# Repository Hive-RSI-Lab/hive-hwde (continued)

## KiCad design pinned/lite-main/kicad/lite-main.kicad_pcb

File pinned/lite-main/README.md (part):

# lite-main: the Lite tier of hifi-receiver-2

The Lite tier's one board, as `docs/product.md` defines it. You plug a USB-C PD
laptop charger of 65 W or more and a pair of speakers into it (Lite asks for
20 V and uses at most what that contract allows, 60–65 W with an ordinary
cable: a bigger charger adds nothing; see issue #136). It streams over Wi-Fi
(Spotify Connect, AirPlay, Lyrion) and Bluetooth, takes a DJ deck on RCA, and
drives two subwoofers from RCA sub outs. A web app on your phone, three buttons
or any IR remote control it.

It was designed with the hive-hwde module (KiCad 10), from schematic to JLC fab
package, on 2026-10-28. **Nothing has been ordered.** Ordering and paying are
the person's. The workspace is named after the board, `boards/lite-main/` (the
brief said `boards/lite/`): that is the path `tools/hwcheck.py` scores, from
product.md's Boards row.

## What it is

- **Board:** 2 layers, 1.6 mm FR-4, 1 oz, OSP, 118 x 90 mm, four M3 holes
  (H1-H3 plated, H4 bare), 2 mm corners. 154 parts, all on the top side. 147 are SMT; 7 are
  through-hole (J2, J3, J4-J7 and U9). The 4 mounting holes are not BOM parts.
  JLC assembly with LCSC part numbers.
- **Rear edge, left to right:**
  - **J2:** RCA line in (FLX4). Top jack white = L, bottom red = R. ESD: D3/D4.
  - **J3:** RCA sub out L/R. ESD: D5/D6.
  - **J1:** USB-C.
  - **J4-J7:** the speaker outputs, four 4 mm banana sockets (Amass 24.243,
    right-angle PCB mount, 24 A, red C7437321 / black C7437322; JLC fits
    them): J4 L+, J5 L-, J6 R+, J7 R-, at 11 mm pitch. Their round collars
    (9.40 mm across, 2.60 mm long, bottom 3.20 mm over the board) reach 2.65 mm
    past the rear edge into the enclosure's 10.2 mm round holes, bore axis
    8.1 mm over the board. Body 10.10 mm wide, 10.70 mm across the rib; pins
    15.5 +/-0.3 mm (Multicomp's sheet for the same part numbers; Amass's says 15.7). Nothing is wired by hand. Single banana plugs;
    the 11 mm pitch is too close for a dual (19 mm) plug.
- **Front edge:** SW1 vol-, SW2 vol+, SW3 play/source (hold = BT pairing),
  the IR receiver U9 (an IRM-3638T standing at the edge with its lens facing
  forward through the front wall) and a red status LED D2.
- **ESP32 antenna:** at the left edge. A copper keep-out on both layers runs
  from 15 mm above it to the bottom edge, and no copper is left in the check's
  15 mm bands either side. H4, 8 mm below the antenna, is a bare unplated hole
  for that reason, so a metal screw there sits near the antenna with no ground
  bond (`docs/boards/lite-preorder.md`).

| Block | Parts | Notes |
|---|---|---|
| USB-C + PD | J1 HRO TYPE-C-31-M-12 (20 V/5 A), U1 CH224A, D1 SMBJ22A; ESD: D7/D8 PESDNC2FD5VB (D+/D-; CC exempt, docs/boards/lite-esd.md) | asks for 20 V (Rset 120k); I2C 0x22 on the codec's bus, so firmware reads the protocol status (0x09) and the PDO's max current (0x50). The CH224A has no SRCCAP registers (CH224Q only). |
| PVDD switch | Q1 AO4485, Q4 MMBT3904 | on only when GPIO18 is high **and** the PD contract is good (Q4's emitter is CH224A PG); C19 holds the gate shut on VBUS steps; soft start ~28 ms, 0.41 A inrush; R16 bleeder |
| 5 V | U2 TPS54302, L5 10 uH | TI design-example values |
| 3.3 V | U3 SY8089 (digital), U4 LP5907 (codec analog) | |
| MCU | U5 ESP32-WROVER-E-N8R8, U6 CH340B, Q2/Q3 | console + flashing over the same USB-C; auto-program on DTR/RTS |
| Codec | U7 ES8388 | pinned like the ESP32-A1S AudioKit (I2S MCLK 0, BCLK 27, LRCK 25, DOUT 26, DIN 35; I2C 32/33): squeezelite-esp32's board profile applies |
| Amp | U8 TPA3118D2, L1-L4 10 uH 8 A, C68-C71 1 uF | BTL, 26 dB, BD mode, no power limit; 2 x 38.7 W into 4 ohm at 20 V, 1 % THD (review-2) |
| Self-measurement | R66-R69, C81-C84 | SPK_L_P / SPK_R_P through 100k/10k, 470 pF, 1 uF into the codec's LIN2/RIN2: the board records its own speaker outputs (ratio 0.0625 with the ADC's input) |
| Bulk | C58 470 uF polymer, C59 220 uF | |

ESP32 pin map:

| GPIO | Signal |
|---|---|
| 0 | MCLK |
| 4 | PD power-good |
| 13 | vol+ |
| 14 | IR |
| 18 | PVDD enable |
| 19 | play |
| 21 | amp SDZ (through 100k) |
| 22 | LED |
| 23 | amp fault |
| 34 | VBUS/11 |
| 39 | PVDD/11 (firmware confirms the switch closed) |
| 36 | vol- |
| 1/3 | UART0, also on spare header J8 |
| 5, 15 | unused by the audio side, on spare header J8 (boot straps) |

The full table is in [`architecture/blocks.md`](architecture/blocks.md). Spare header J8:
[`docs/boards/lite-header.md`](../../docs/boards/lite-header.md).

## First-spin review (review-2, 2026-10-29)

Six independent reviewers (power, audio, digital/RF, thermal, DFM, parts
pin-to-pad) read this board from its KiCad files and the vendor datasheets:
[`docs/review-2/`](../../docs/review-2/). No pinout errors. What changed on
this board because of it:

| Finding | Was | Now |
|---|---|---|
| AUDIO-4 / DIGITAL-14 (major): the amp could stay in shutdown, since SDZ's up-to-50 uA input current through 100k left it under 2 V | R54 100k | R54 10k (SDZ >= 2.7 V) + C26 47 nF slew limit |
| POWER-3 (major): Q1 turned itself on at every VBUS step with the firmware off (C2 Miller coupling) | R6 47k | R6 220k + C19 4.7 uF gate-source (Vsg <= 6.6 V, so 16 V 0603) |
| POWER-4 (major): firmware turn-on at the AO4485 SOA edge, 2.5 A inrush on a 3 A contract | 6 ms ramp | 28 ms ramp, 0.41 A, 5.8 W peak (simulated, >3x SOA margin) |
| AUDIO-7: 1.5-2 dB line-in headroom at the FLX4's 2.1 Vrms | R30/R33 10k | 15k: -4.2 dBFS |
| POWER-10: 5 V buck crossover above TI's 40 kHz | C9 100 pF, 2 x 22 uF | C9 47 pF, + C25 22 uF |
| DFM-2: RCA pin rows ambiguous on the maker's drawing | round pin holes, 1.7 x 2.4 leg holes | pins 1/3 are 1.6 x 2.4 plated slots covering both readings; legs 2.0 x 3.0 as drawn |
| Stock: USB4105 0 free at JLC; CH340C not buyable | USB4105, CH340C | HRO TYPE-C-31-M-12 (20 V, Lite asks 20 V), CH340B |

THERMAL-3 (continuous full power trips the latched OTP) and AUDIO-6
(0 dBFS overdrives the amp by 4.1 dB) are firmware's:
[`docs/review-2/firmware-requirements.md`](../../docs/review-2/firmware-requirements.md).
Every fact the board relies on is in [`docs/known-unknowns.md`](../../docs/known-unknowns.md)
(`python3 tools/known_unknowns.py --check` before ordering).

The changes went in as an ECO on the routed board, keeping all other
copper: `kicad/gen/eco_swap.py` (J1/U6 swaps; J1's VBUS/GND pads made plain
0.6 mm rectangles and its signal pads trimmed to the USB4105's inner edge),
`eco_rca.py`, then `board_update` with `find_spots.py` placements, and the new
nets routed with `miniroute.py`/`add_track.py`/`add_via.py`. Freerouting timed
out twice on the routed board under the machine's load.

## Design decisions, and why

Each one is also in `state.json` (`decisions`). The schematic review and what
was done about each finding is in
[`reports/review-schematic-response.md`](reports/review-schematic-response.md).

- **CH224A, not the CH224Q product.md named.** Same die and registers. The
  CH224Q's 2 x 2 mm, 0.4 mm-pitch DFN puts VBUS between CC1 and CFG1, right
  under the USB-C, and it couldn't be fanned out on 2 layers. The ESSOP-10 is
  1.0 mm pitch, same price, 9.5k in stock. The CH224K has 1 in stock.
- **The CC lines are crossed on purpose.** The CH224 treats CC1/CC2 alike, so
  J1's B5 goes to U1 pin 7 and A5 to pin 6. That way neither crosses the
  other or the D+/D- escape.
- **Banana sockets on the board, not binding posts wired to a terminal**
  (task 261030-140102: the person orders, plugs in and does nothing else).
  Amass 24.243 is the only board-mount 4 mm socket JLC stocks (GC4010-F is a
  panel bullet connector). Four at 10.1 mm wide didn't fit the 100 mm edge
  beside USB-C and the RCA jacks, so the board grew to 118 mm east; H2 moved
  under the sockets to (114.45, 27). The L row moved 2.2 mm toward U8, and
  the 1 uF output caps (C68-C71) and R68 sit between the sockets' backs and
  the inductors. `kicad/gen/banana_route.py` is the speaker copper: L+ and R+
  on F.Cu, L- and R- through seven vias each (3.5 A) on B.Cu under the
  sockets. Both pins of each socket are its contact and carry the current.
- **Amp channels swapped at the chip.** The TPA3118's "right" channel drives
  the left speaker, so its output row runs L+ L- R+ R- straight into the
  terminal with no crossing. Nets are named by speaker channel.
- **PVDD needs firmware and the PD contract.** GPIO18 AND CH224A PG (hardware
  AND through Q4's emitter). A 5 V laptop port can never power the amp, and
  the firmware can drop it before a PD renegotiation.
- **5 V buck is a TPS54302**, not the SY8303 in the cost estimate: TI's
  datasheet design example gives every value. 5.18 V (100k/13k, Basic parts).
- **SMBJ22A TVS** (BORN C151920; standoff 22 V, breakdown 24.4–26.9 V,
  clamp 35.5 V at 16.9 A). PD allows 20 V +5 %, so the rail can sit at 21 V:
  the SMBJ20A first fitted had a 20 V standoff, under that, and hwde's USB-C
  PD sink rule asks for working >= 22 V. A 22 V part is the lowest standoff
  that holds 21 V; it still breaks down below the 30 V abs-max of the
  TPS54302 and TPA3118. Same SMB footprint, pin 1 = cathode. No TVS can
  hold a 21 V bus under 30 V at its full rated surge; that residual risk is
  review-2 POWER-9 (PD attaches at 5 V, so real surge energy is small).
- **TPA3118 gain 26 dB.** The ES8388's full scale (~0.9 Vrms) x 20 clips at
  20 V into 4 ohm 3.7 dB before 0 dBFS, so firmware caps the codec volume.
  20 dB would leave only 20 W.
- **Power copper is pours, not tracks.** VBUS (J1 to Q1) and PVDD carry up
  to 5 A, joined by 16 vias. PVDD runs from Q1's drain down a B.Cu column
  under the filter caps, so the speaker lines cross it on F.Cu. It continues
  as a B.Cu pour under the inductors, stopping 5 mm short of the amp so the
  ground under it is unbroken, then F.Cu islands at both PVCC groups. The pours
  are in `kicad/gen/power.py`. Tracks only feed the small taps.
- **Amp OUT runs (pin to inductor) are 0.31 mm minimum** at the HTSSOP pins
  (0.65 mm pitch, 0.34 mm pins), sized for 1.0 A rms / 30 C. That is music at
  full power with a 9 dB crest factor. They are under 15 mm long. The
  inductor-to-socket runs are 1.25 mm (3.5 A, 30 C).
- **USB is not impedance-controlled.** Full speed, 12 Mb/s; a 90 ohm pair on
  1.6 mm 2-layer would be 1.1 mm wide.
- **USB ESD:** D7/D8 (PESDNC2FD5VB) are fitted on D+/D-; the CC pins have no
  clamp (docs/boards/lite-esd.md).
- **Board 118 x 90 mm**, not the ~100 x 80 product.md estimated: 80 left no
  room for the PVDD switch between USB-C and the amp, and the banana sockets
  took 18 mm more.
- **Red LED (Basic part) at 1.3 mm.** The white one the first schematic had ran
  at 0.2-0.6 mA, too dim.
- **IR on GPIO14**, not 39: GPIO36/39 glitch with ADC/Wi-Fi (errata 3.11).
  vol- stays on 36; a polled, debounced button tolerates the glitch. GPIO39
  reads PVDD/11 instead (firmware worker's ask), which is sampled, not edge-triggered.
- **Front-facing IR receiver.** The enclosure worker found the top-looking
  IRM-H638T would sit 31 mm under the lid, outside a remote's 45 degree cone.
  It is now a through-hole IRM-3638T whose lens faces through the front wall,
  with Everlight's 100 ohm / 4.7 uF supply filter.

## The checks it passed

The pre-order round of 2026-11-01 (hwde 0600487: vias off pads, I2S respaced, VBUS stubs, box holes) is in `docs/boards/lite-preorder.md`.

| Gate | Result |
|---|---|
| ERC (`erc`) | 0 errors, 0 warnings (every pulled pin is typed passive, so the schematic review checked pins by hand) |
| Placement (`place`) | pass, 0 errors |
| Routed DRC (`drc_routed`) | 0 errors, 0 warnings, 0 unconnected |
| Verify suite (`verify`) | pass, with one signed waiver (U8 thermal, below) and 44 warnings, now shown by hwde e225475: 25 route-style (off-45 jogs in Freerouting and maze-router copper; DRC-clean, cosmetic), 18 part ratings with no datasheet extraction (each part's voltage and current margin is in `docs/review-2/` instead), 1 decoupler 5.3 mm from U8 pin 31 (C57, 1 nF HF cap, limit 5.0; 0.3 mm over, left) |
| JLC DFM on the exported Gerbers (`dfm`) | pass, 0 errors. 3 warnings: thin silk strokes inside stock/EasyEDA footprints, and J2/J3's LCSC model pad centre 0.79 mm off. The LCSC model itself has pad 3 0.8 mm off pad 1 in Y, where the real jack and our footprint have them level. Since 2026-11-04 the CPL places J2/J3 at the footprint origin (hwde 7f65e45; `cpl_verify` 0.0 mm). They are through-hole, so their holes locate them; check them in JLC's preview. Every CPL rotation was checked against the LCSC model. |

All gates last passed on hive-hwde c23e27e (2026-10-29), after the review-2 ECO.

**The one waiver: TPA3118 thermal**
([`reports/verify-waivers.json`](reports/verify-waivers.json)):

- **The two estimates:** hwde's copper-area model gives the amp ~47 C/W on
  this board, which is ~94 C rise at 2 W (1/8 power into 4 ohm). TI's
  datasheet gives 22 C/W for this package on its 2-layer EVM, ~44 C rise.
- **What the board does about it:** both sides are ground-poured around the
  chip, with 16 solid EP vias and unbroken B.Cu ground under it.
- **Backstops:** the chip shuts itself down on over-temperature and reports it
  on FAULTZ, which the firmware reads.
- **Bring-up must measure it** at 1/8 power into 4 ohm. Above 100 C, stick a
  heatsink on the package top or lower the governor's limit.

**Reviews:**

- **Schematic:** a fresh-context review found 1 error and 14 warnings,
  answered in
  [`reports/review-schematic-response.md`](reports/review-schematic-response.md).
- **Routed board:** [`reports/review-board.md`](reports/review-board.md).

**Hand checks, 2026-11-04** (hwde `check_esd`, `check_body_clash`, the 3D
clash and `check_model_paths`/`check_model_fit`, on main 5b7f956). None of
these is in the CI gates. 0 errors on every check. The warnings:

- **ESD:** 10 warnings, all accepted in
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
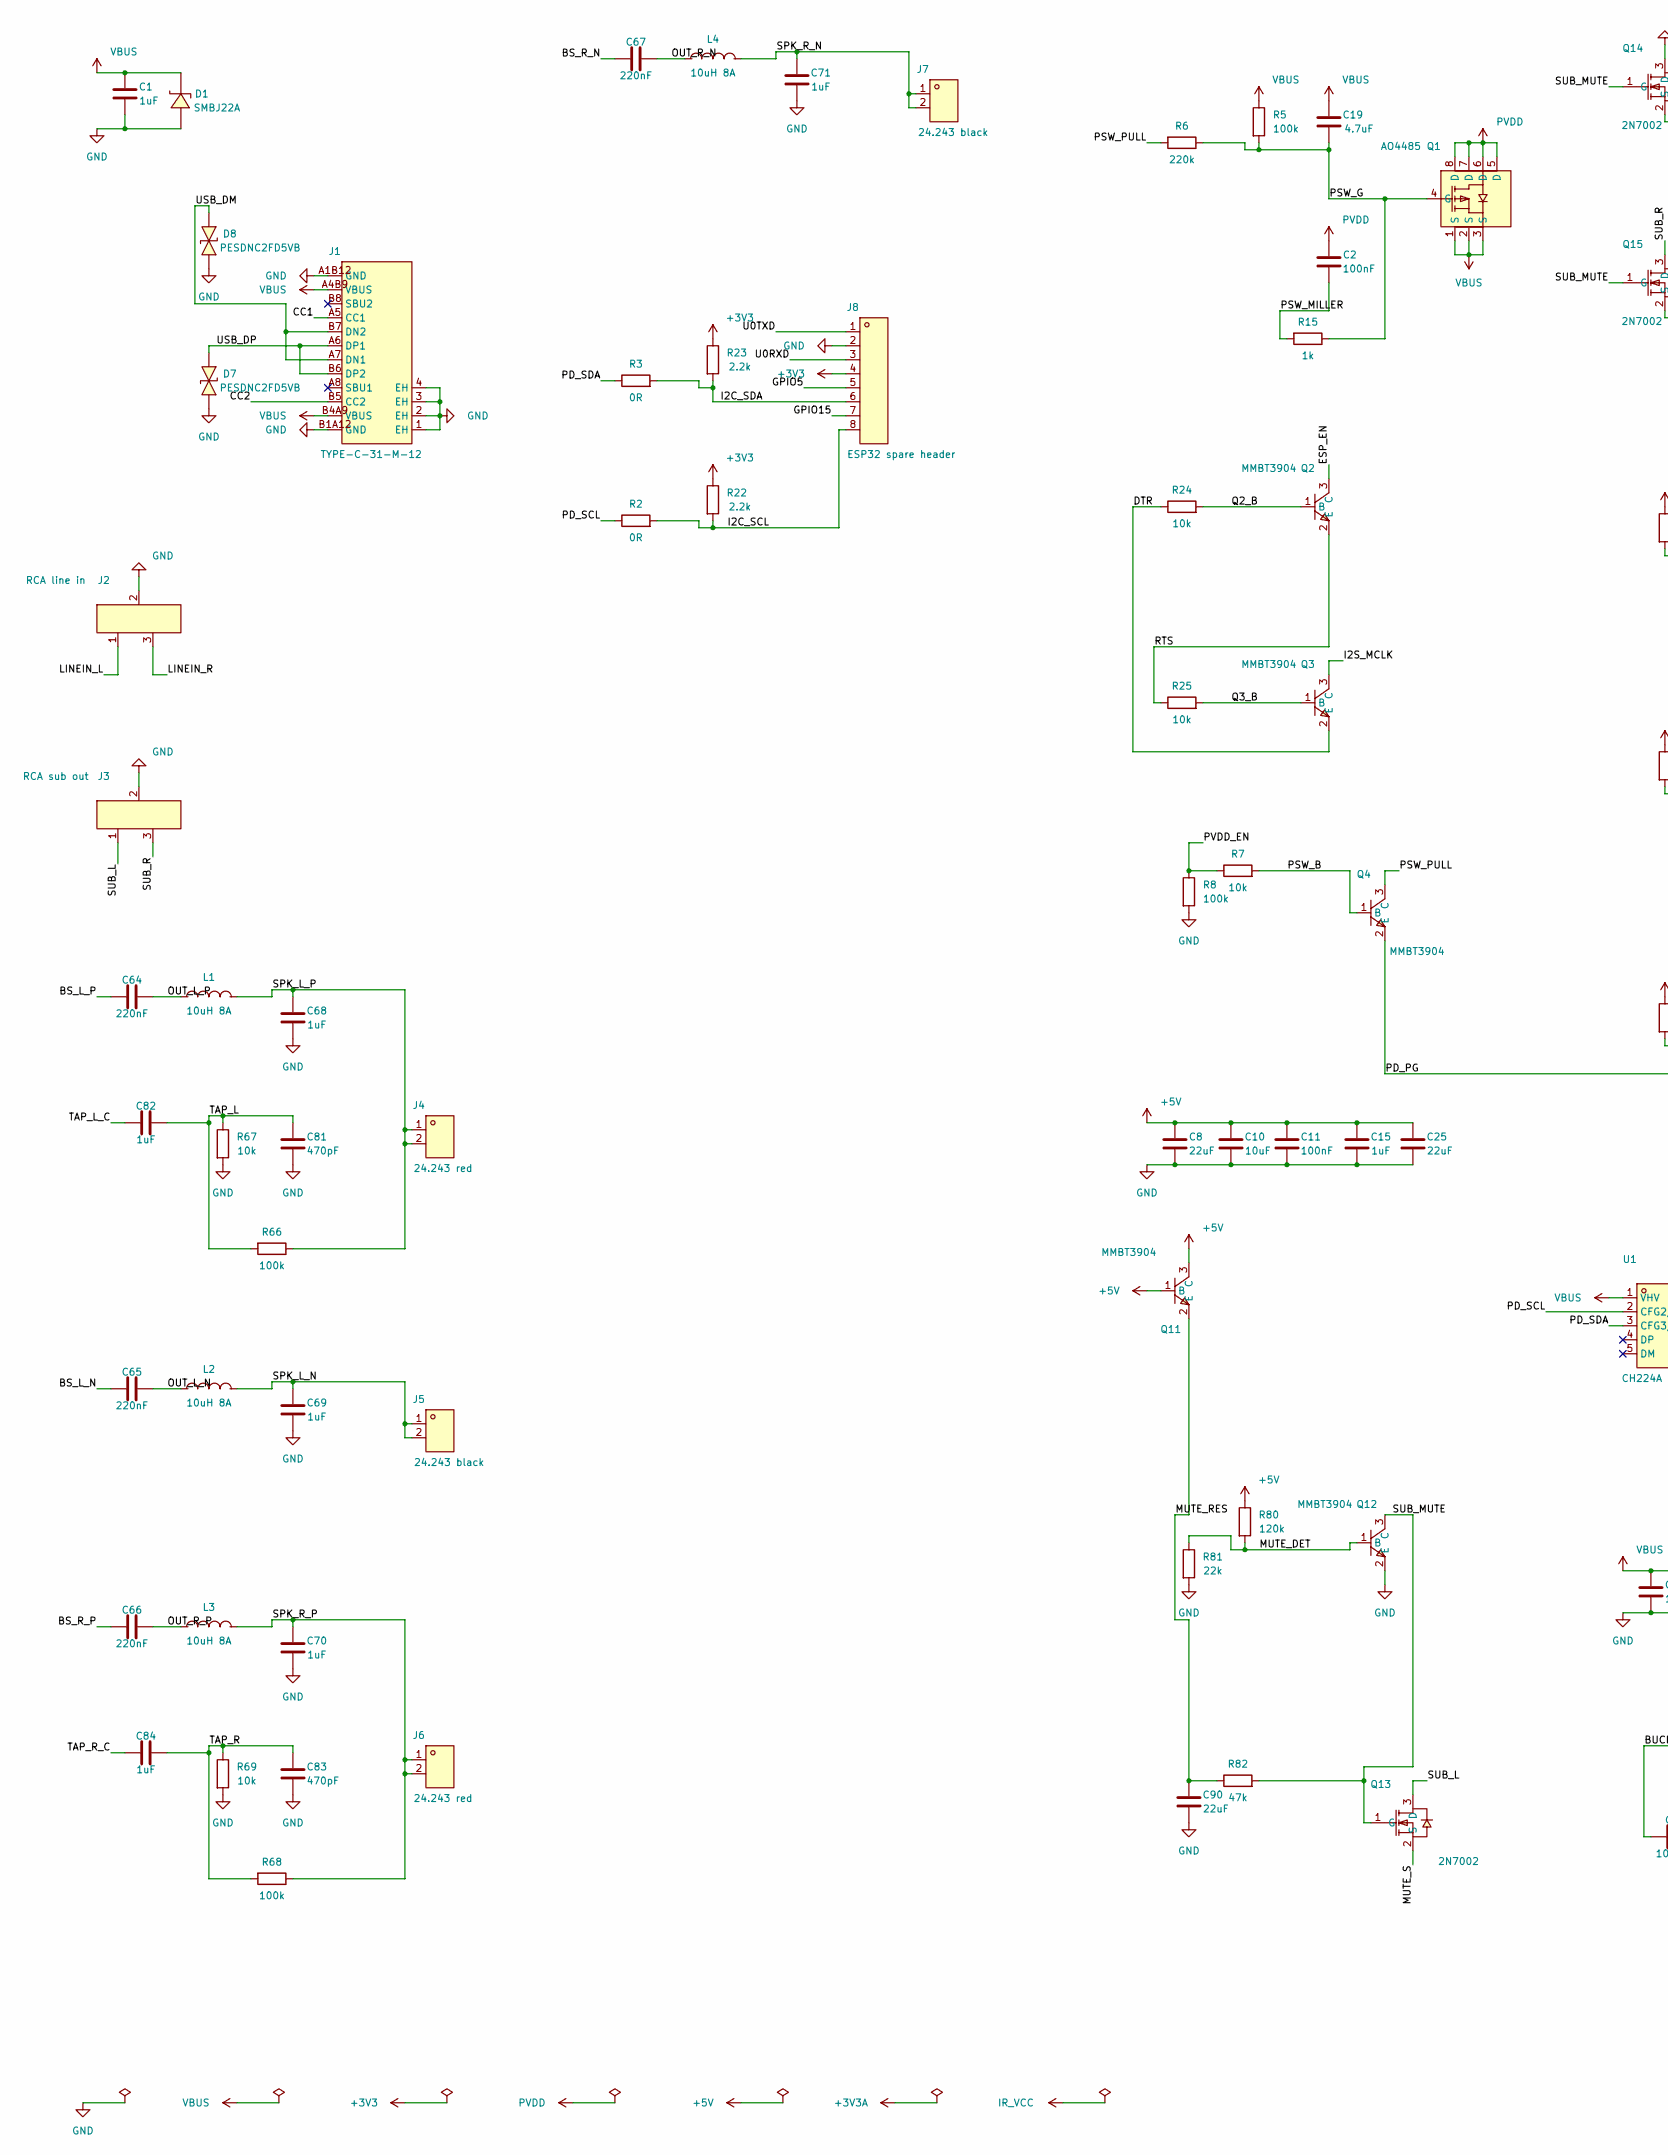
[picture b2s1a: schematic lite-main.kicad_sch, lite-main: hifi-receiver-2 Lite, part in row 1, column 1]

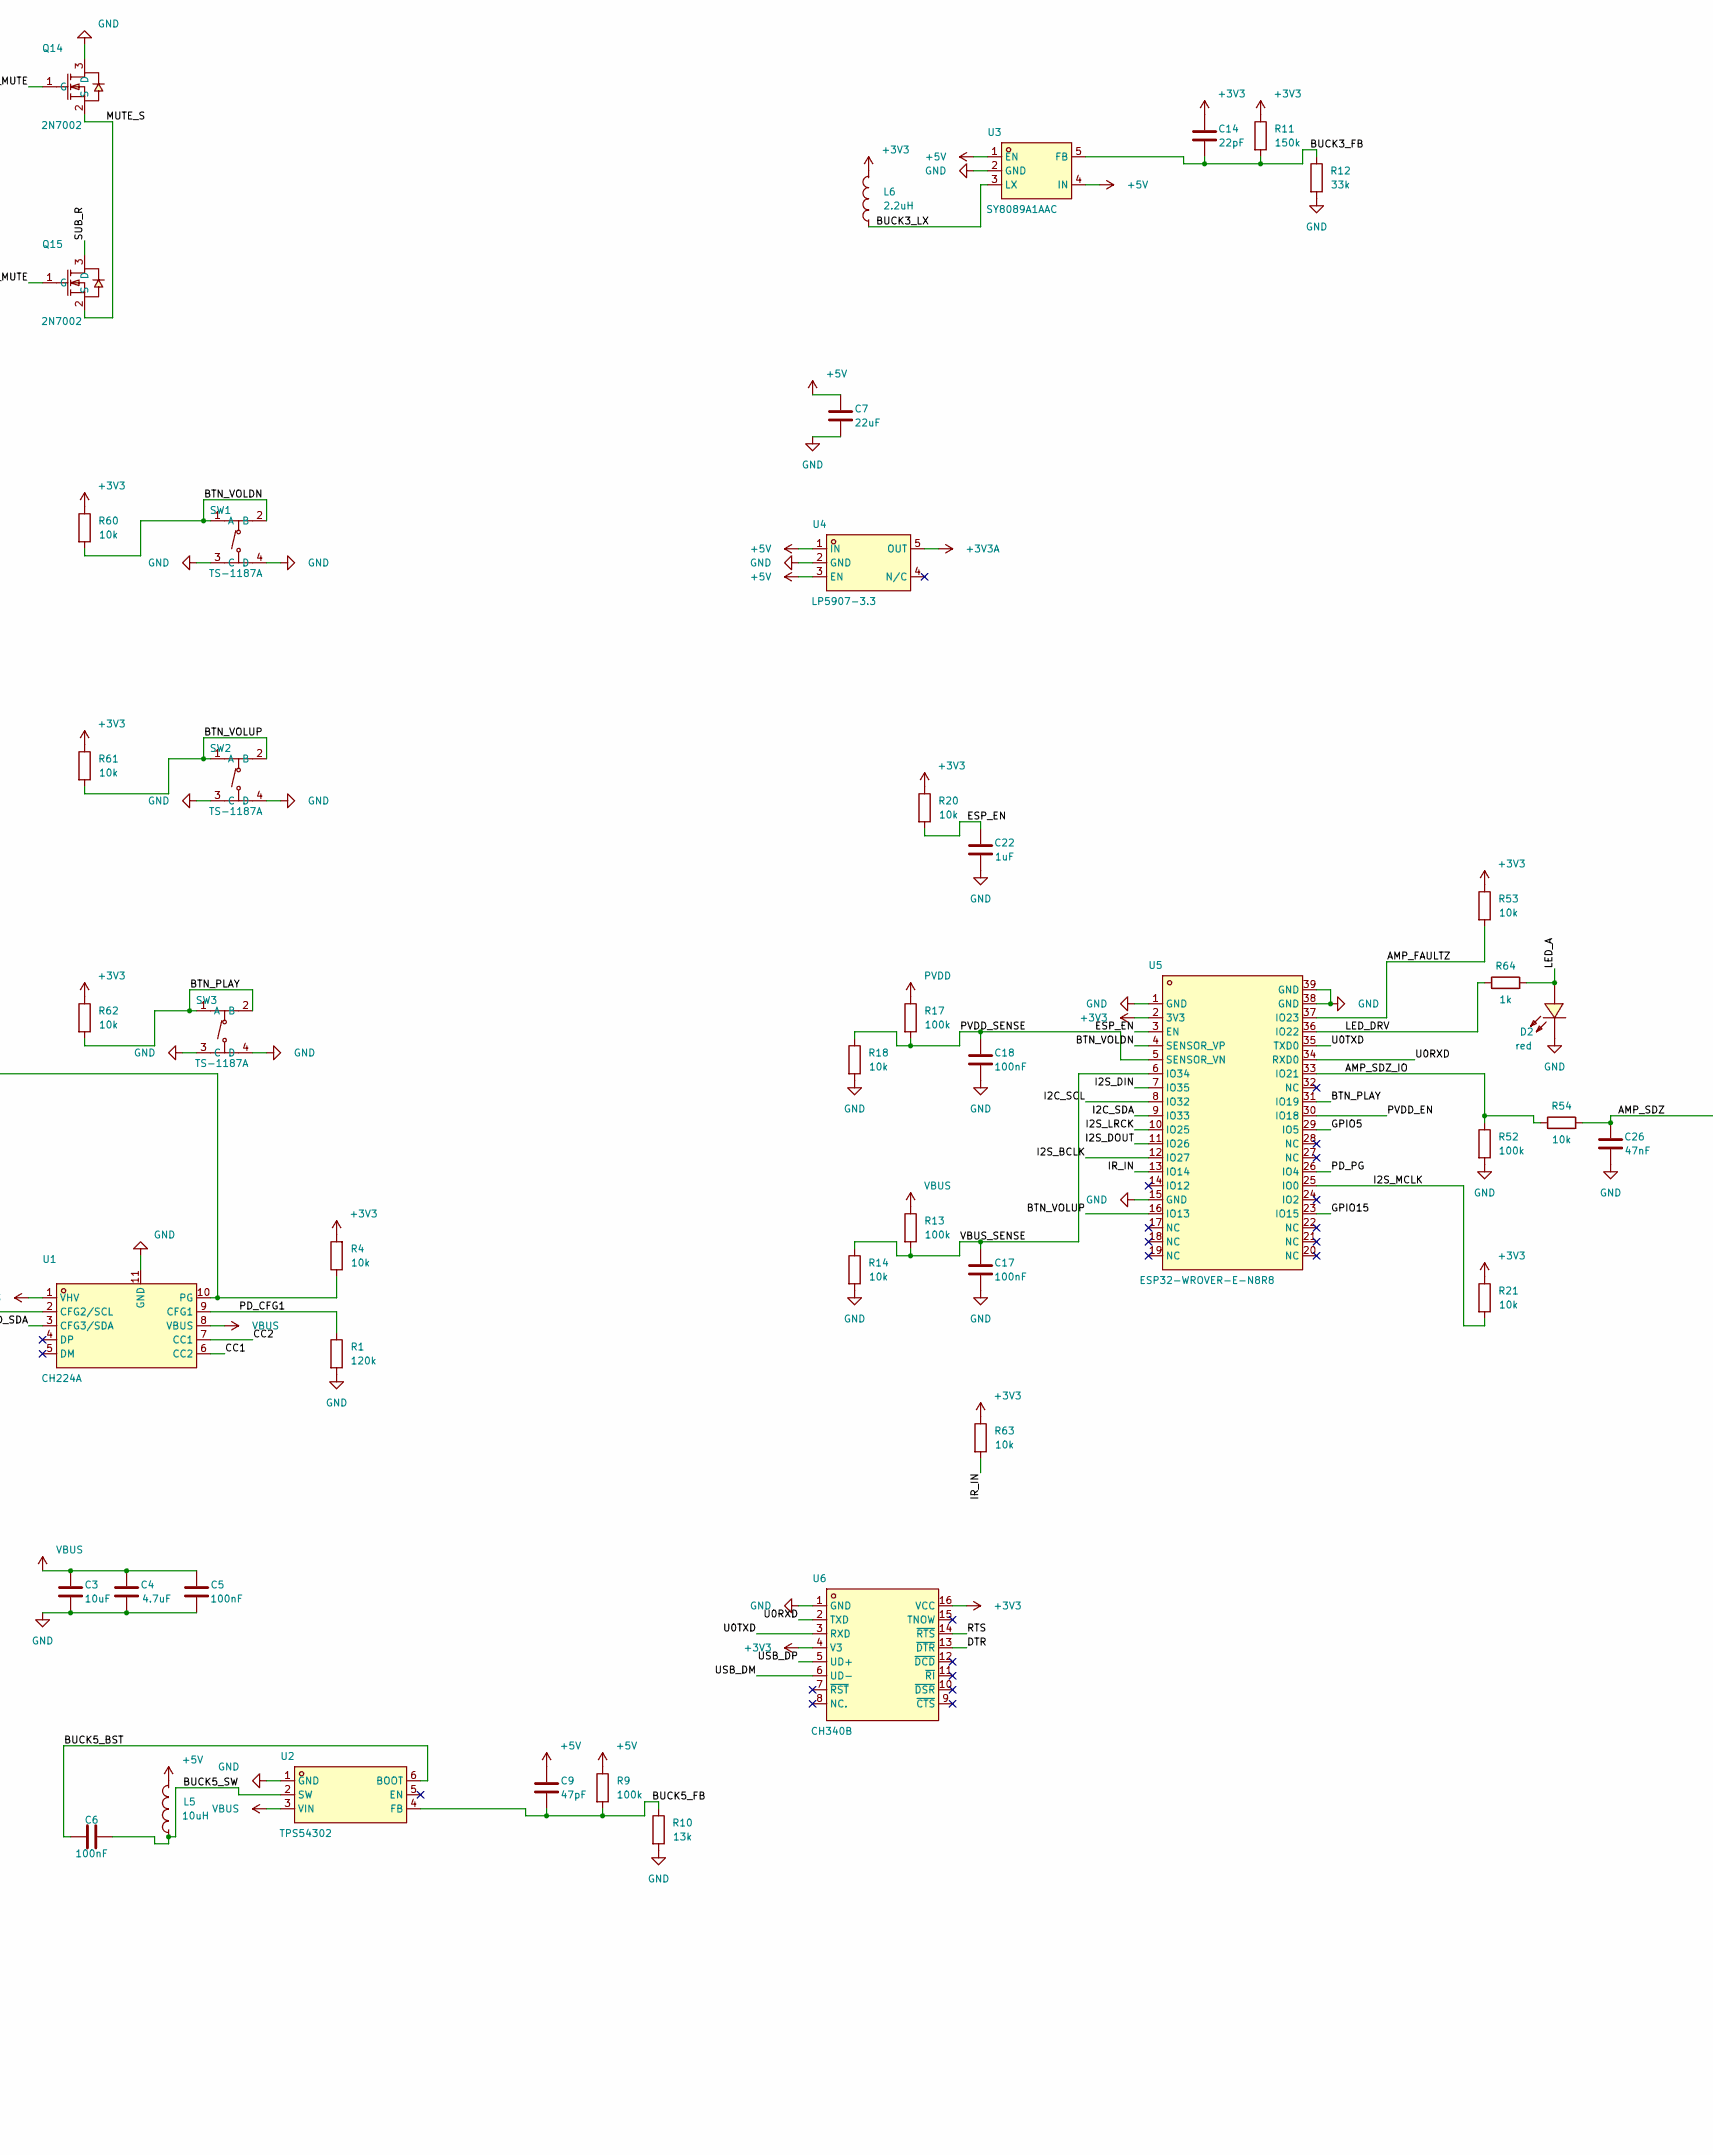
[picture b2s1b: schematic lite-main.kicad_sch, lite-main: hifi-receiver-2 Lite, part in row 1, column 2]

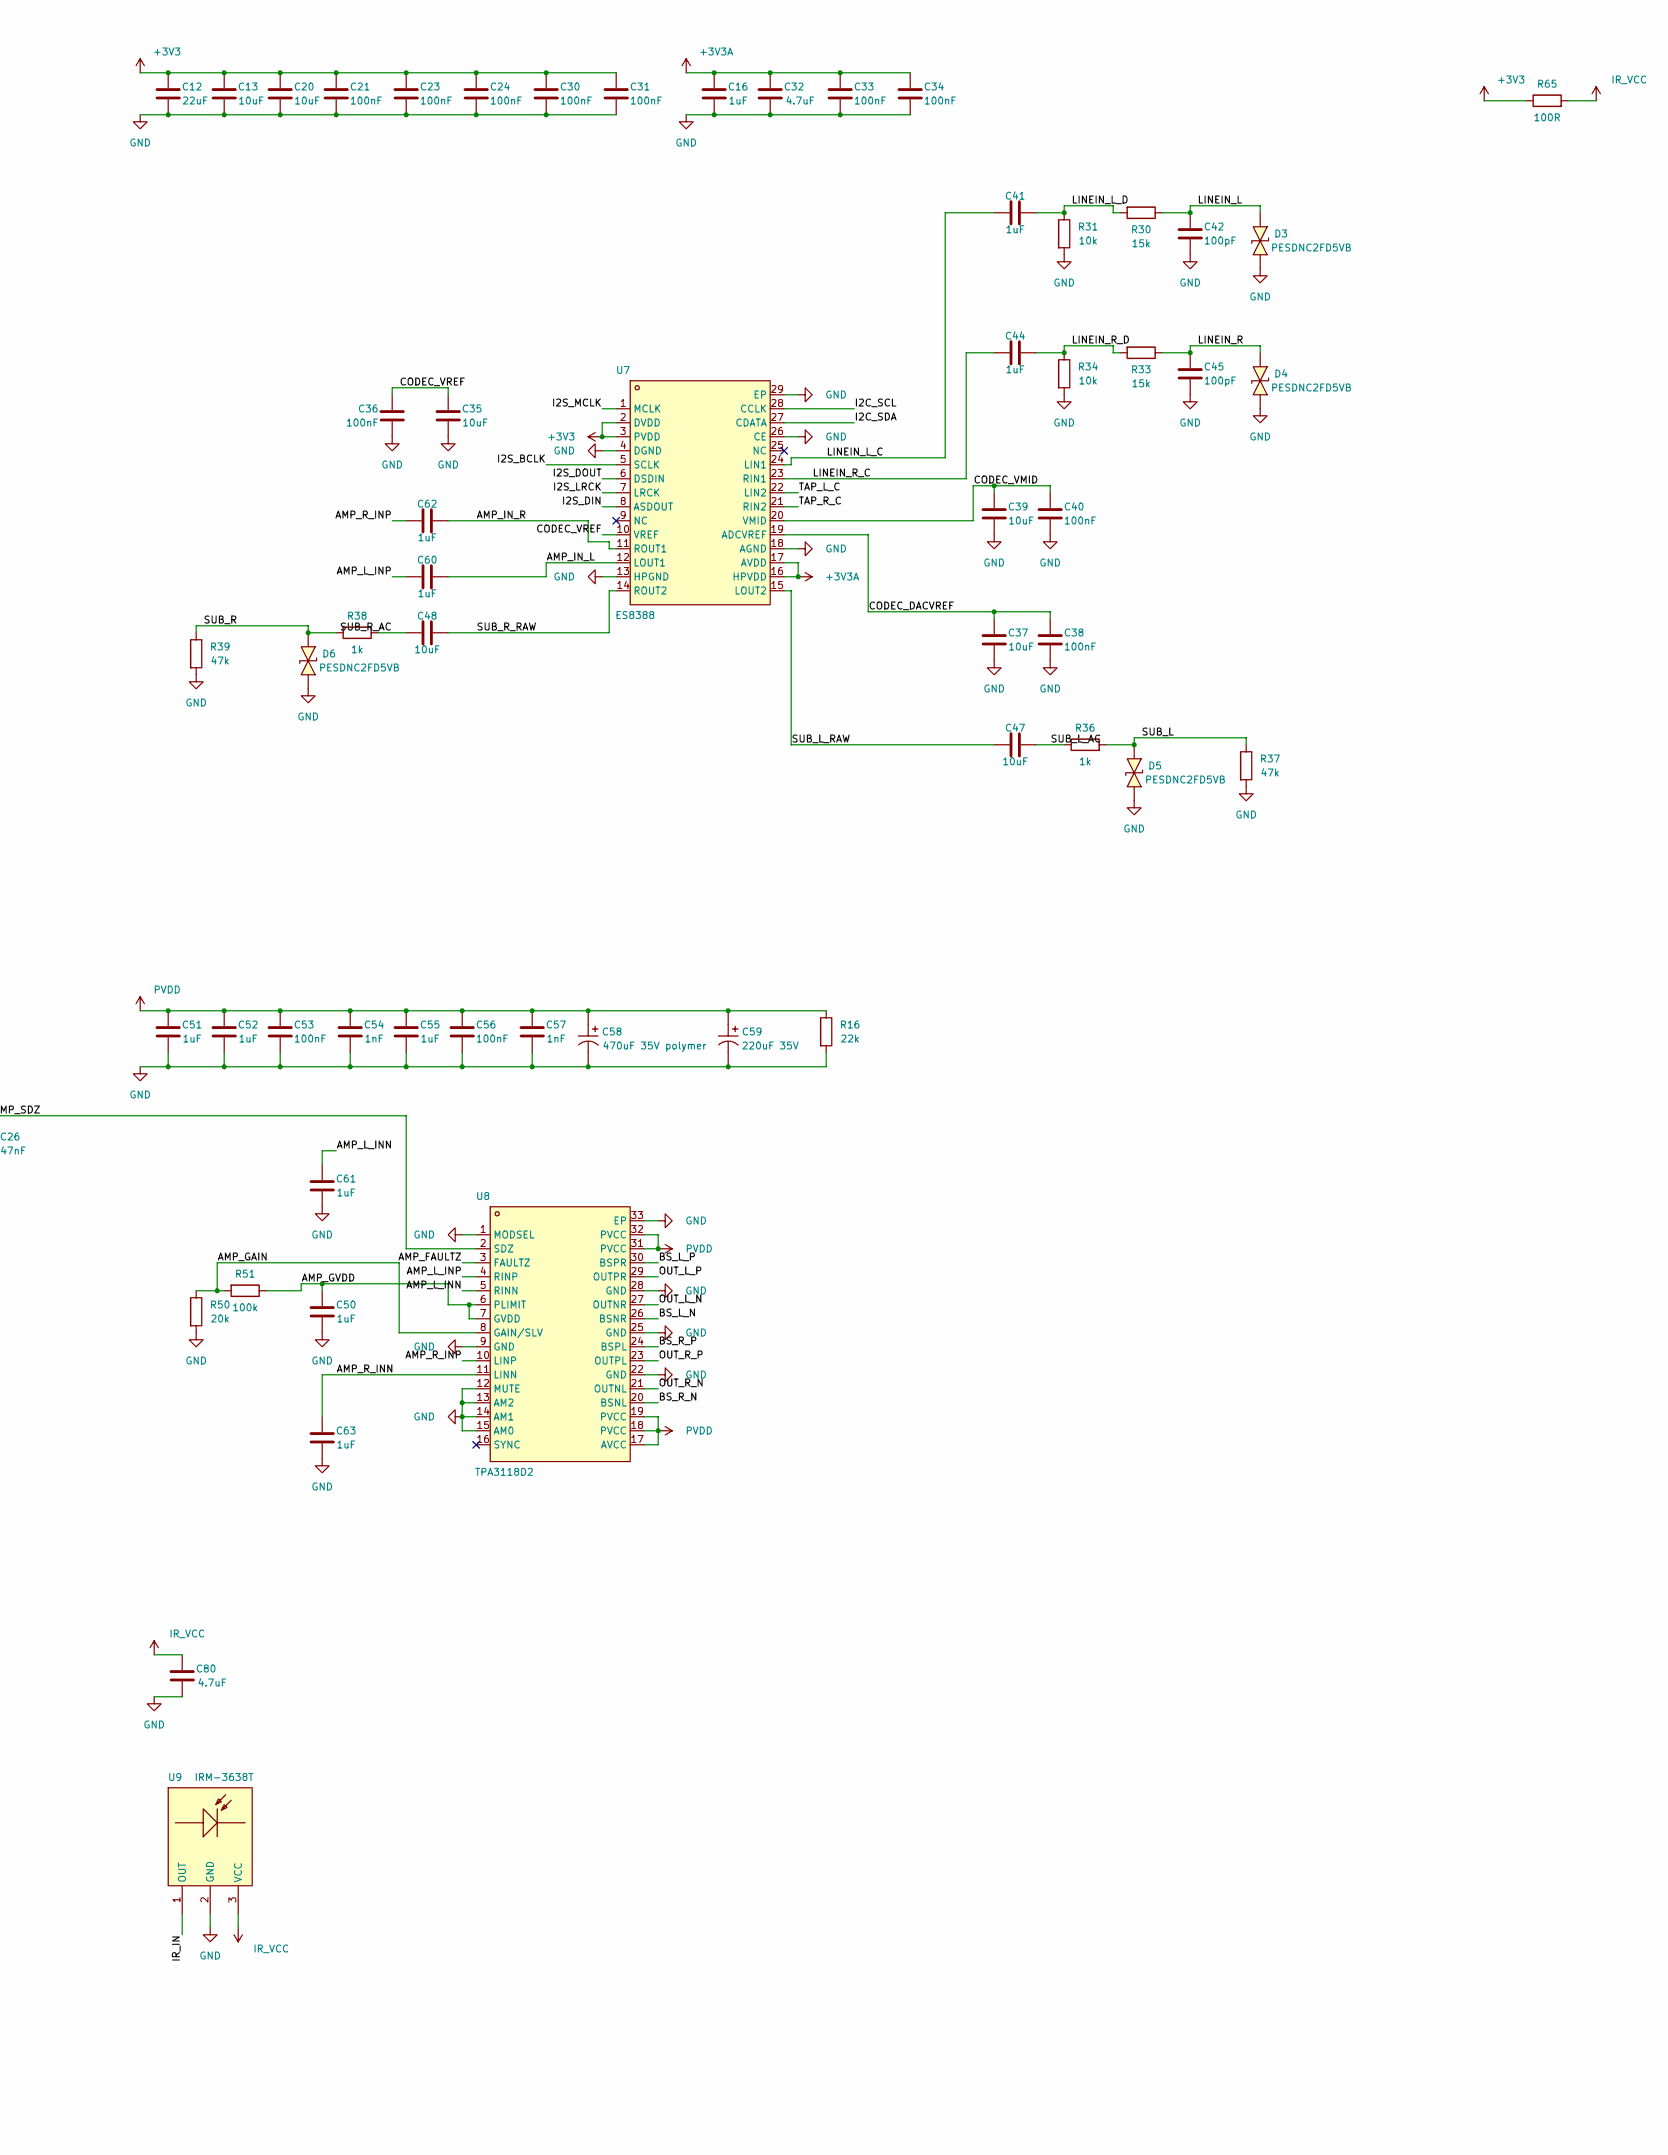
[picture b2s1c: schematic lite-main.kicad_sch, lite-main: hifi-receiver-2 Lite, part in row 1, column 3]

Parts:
C1, C15, C16, C22, C41, C44, C50, C60, C61, C62, C63, C82, C84: 1uF; C_0603_1608Metric; LCSC C15849
C2, C5, C6, C11, C17, C18, C21, C23, C24, C30, C31, C33, C34, C36, C38, C40, C53, C56: 100nF; C_0603_1608Metric; LCSC C14663
C3: 10uF; C_1206_3216Metric; LCSC C13585
C4: 4.7uF; C_1206_3216Metric; LCSC C29823
C7, C8, C12, C25, C90: 22uF; C_0805_2012Metric; LCSC C45783
C9: 47pF; C_0603_1608Metric; LCSC C1671
C10, C13, C20, C35, C37, C39, C47, C48: 10uF; C_0603_1608Metric; LCSC C19702
C14: 22pF; C_0603_1608Metric; LCSC C1653
C19, C32, C80: 4.7uF; C_0603_1608Metric; LCSC C19666
C26: 47nF; C_0603_1608Metric; LCSC C1622
C42, C45: 100pF; C_0603_1608Metric; LCSC C14858
C51, C52, C55: 1uF; C_0805_2012Metric; LCSC C28323
C54, C57: 1nF; C_0603_1608Metric; LCSC C1588
C58: 470uF 35V polymer; CAP-SMD_BD10.0-L10.3-W10.3-FD-LS11.0; LCSC C46550472
C59: 220uF 35V; CAP-SMD_BD8.0-L8.3-W8.3-LS9.3-FD; LCSC C2836441
C64, C65, C66, C67: 220nF; C_0603_1608Metric; LCSC C21120
C68, C69, C70, C71: 1uF; C_1206_3216Metric; LCSC C1848
C81, C83: 470pF; C_0603_1608Metric; LCSC C1620
D1: SMBJ22A; SMB_L4.6-W3.6-LS5.3-RD; LCSC C151920
D2: red; LED-SMD_L1.6-W0.8-R-RD; LCSC C2286
D3, D4, D5, D6, D7, D8: PESDNC2FD5VB; DFN1006-2L-BI; LCSC C110694
J1: TYPE-C-31-M-12; USB-C_SMD-TYPE-C-31-M-12_1; LCSC C165948
J2: RCA line in; CONN-TH_XDJK-0271-1650; LCSC C7527522
J3: RCA sub out; CONN-TH_XDJK-0271-1650; LCSC C7527522
J4, J6: 24.243 red; CONN-TH_24.243.1_RED; LCSC C7437321
J5, J7: 24.243 black; CONN-TH_24.243.2; LCSC C7437322
J8: ESP32 spare header; HDR-SMD_8P-P2.54-V-M-LS4.8_R2; LCSC C2883765
L1, L2, L3, L4: 10uH 8A; IND-SMD_L8.0-W8.0_XR0850; LCSC C48391614
L5: 10uH; IND-SMD_L6.0-W6.0_SWPA6045S; LCSC C79272
L6: 2.2uH; IND-SMD_L4.0-W4.0_VLCF4020; LCSC C305171
Q1: AO4485; SOP-8_L4.9-W3.9-P1.27-LS6.0-BL; LCSC C5125949
Q2, Q3, Q4, Q11, Q12: MMBT3904; SOT-23-3_L2.9-W1.3-P1.90-LS2.4-BR; LCSC C20526
Q13, Q14, Q15: 2N7002; SOT-23-3_L2.9-W1.3-P1.90-LS2.4-BR; LCSC C8545
R1, R80: 120k; R_0603_1608Metric; LCSC C25808
R2, R3: 0R; R_0603_1608Metric; LCSC C21189
R4, R7, R14, R18, R20, R21, R24, R25, R31, R34, R53, R54, R60, R61, R62, R63, R67, R69: 10k; R_0603_1608Metric; LCSC C25804
R5, R8, R9, R13, R17, R51, R52, R66, R68: 100k; R_0603_1608Metric; LCSC C25803
R6: 220k; R_0603_1608Metric; LCSC C22961
R10: 13k; R_0603_1608Metric; LCSC C22797
R11: 150k; R_0603_1608Metric; LCSC C22807
R12: 33k; R_0603_1608Metric; LCSC C4216
R15, R36, R38, R64: 1k; R_0603_1608Metric; LCSC C21190
R16, R81: 22k; R_0603_1608Metric; LCSC C31850
R22, R23: 2.2k; R_0603_1608Metric; LCSC C4190
R30, R33: 15k; R_0603_1608Metric; LCSC C22809
R37, R39, R82: 47k; R_0603_1608Metric; LCSC C25819
R50: 20k; R_0603_1608Metric; LCSC C4184
R65: 100R; R_0603_1608Metric; LCSC C22775
SW1, SW2, SW3: TS-1187A; SW-SMD_4P-L5.1-W5.1-P3.70-LS6.5-TL_H1.5; LCSC C318884
U1: CH224A; ESSOP-10_L4.9-W3.9-P1.0-LS6.0-TL-EP; LCSC C42459160
U2: TPS54302; SOT-23-6_L2.9-W1.6-P0.95-LS2.8-BL; LCSC C311983
U3: SY8089A1AAC; TSOT-23-5_L2.9-W1.6-P0.95-LS2.8-BR; LCSC C479074
U4: LP5907-3.3; SOT-23-5_L3.0-W1.7-P0.95-LS2.8-BR; LCSC C80670
U5: ESP32-WROVER-E-N8R8; WIFI-SMD_ESP32-WROVER-IE8MB; LCSC C2973667
U6: CH340B; SOP-16_L10.0-W3.9-P1.27-LS6.0-BL; LCSC C81010
U7: ES8388; QFN-28_L4.0-W4.0-P0.45-BL-EP; LCSC C365736
U8: TPA3118D2; HTSSOP-32_L11.0-W6.1-P0.65-LS8.1-BL-EP; LCSC C46497
U9: IRM-3638T; OPTO-TH_IRM-3638T; LCSC C42421366

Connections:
+3V3: C12.1, C13.1, C14.1, C20.1, C21.1, C23.1, C24.1, C30.1, C31.1, J8.4, L6.2, R4.2, R11.1, R20.1, R21.1, R22.1, R23.1, R53.1, R60.1, R61.1, R62.1, R63.1, R65.1, U5.2 (3V3), U6.4 (V3), U6.16 (VCC), U7.2 (DVDD), U7.3 (PVDD)
+3V3A: C16.1, C32.1, C33.1, C34.1, U4.5 (OUT), U7.16 (HPVDD), U7.17 (AVDD)
+5V: C7.1, C8.1, C9.1, C10.1, C11.1, C15.1, C25.1, L5.2, Q11.1 (B), Q11.3 (C), R9.1, R80.1, U3.1 (EN), U3.4 (IN), U4.1 (IN), U4.3 (EN)
/AMP_FAULTZ: R53.2, U5.37 (IO23), U8.3 (FAULTZ)
/AMP_GAIN: R50.1, R51.2, U8.8 (GAIN/SLV)
/AMP_GVDD: C50.1, R51.1, U8.6 (PLIMIT), U8.7 (GVDD)
/AMP_IN_L: C60.1, U7.12 (LOUT1)
/AMP_IN_R: C62.1, U7.11 (ROUT1)
/AMP_L_INN: C61.1, U8.5 (RINN)
/AMP_L_INP: C60.2, U8.4 (RINP)
/AMP_R_INN: C63.1, U8.11 (LINN)
/AMP_R_INP: C62.2, U8.10 (LINP)
/AMP_SDZ: C26.1, R54.2, U8.2 (SDZ)
/AMP_SDZ_IO: R52.1, R54.1, U5.33 (IO21)
/BS_L_N: C65.1, U8.26 (BSNR)
/BS_L_P: C64.1, U8.30 (BSPR)
/BS_R_N: C67.1, U8.20 (BSNL)
/BS_R_P: C66.1, U8.24 (BSPL)
/BTN_PLAY: R62.2, SW3.1 (A), SW3.2 (B), U5.31 (IO19)
/BTN_VOLDN: R60.2, SW1.1 (A), SW1.2 (B), U5.4 (SENSOR_VP)
/BTN_VOLUP: R61.2, SW2.1 (A), SW2.2 (B), U5.16 (IO13)
/BUCK3_FB: C14.2, R11.2, R12.1, U3.5 (FB)
/BUCK3_LX: L6.1, U3.3 (LX)
/BUCK5_BST: C6.1, U2.6 (BOOT)
/BUCK5_FB: C9.2, R9.2, R10.1, U2.4 (FB)
/BUCK5_SW: C6.2, L5.1, U2.2 (SW)
/CC1: J1.A5 (CC1), U1.6 (CC2)
/CC2: J1.B5 (CC2), U1.7 (CC1)
/CODEC_DACVREF: C37.1, C38.1, U7.19 (ADCVREF)
/CODEC_VMID: C39.1, C40.1, U7.20 (VMID)
/CODEC_VREF: C35.1, C36.1, U7.10 (VREF)
/DTR: Q3.2 (E), R24.1, U6.13 (~DTR)
/ESP_EN: C22.1, Q2.3 (C), R20.2, U5.3 (EN)
/GPIO5: J8.5, U5.29 (IO5)
/GPIO15: J8.7, U5.23 (IO15)
/I2C_SCL: J8.8, R2.2, R22.2, U5.8 (IO32), U7.28 (CCLK)
/I2C_SDA: J8.6, R3.2, R23.2, U5.9 (IO33), U7.27 (CDATA)
/I2S_BCLK: U5.12 (IO27), U7.5 (SCLK)
/I2S_DIN: U5.7 (IO35), U7.8 (ASDOUT)
/I2S_DOUT: U5.11 (IO26), U7.6 (DSDIN)
/I2S_LRCK: U5.10 (IO25), U7.7 (LRCK)
/I2S_MCLK: Q3.3 (C), R21.2, U5.25 (IO0), U7.1 (MCLK)
/IR_IN: R63.2, U5.13 (IO14), U9.1 (OUT)
/LED_A: D2.1 (A), R64.2
/LED_DRV: R64.1, U5.36 (IO22)
/LINEIN_L: C42.1, D3.1, J2.1, R30.1
/LINEIN_L_C: C41.2, U7.24 (LIN1)
/LINEIN_L_D: C41.1, R30.2, R31.1
/LINEIN_R: C45.1, D4.1, J2.3, R33.1
/LINEIN_R_C: C44.2, U7.23 (RIN1)
/LINEIN_R_D: C44.1, R33.2, R34.1
/MUTE_DET: Q12.1 (B), R80.2, R81.1
/MUTE_RES: C90.1, Q11.2 (E), R82.1
/MUTE_S: Q13.2 (S), Q14.2 (S), Q15.2 (S)
/OUT_L_N: C65.2, L2.1, U8.27 (OUTNR)
/OUT_L_P: C64.2, L1.1, U8.29 (OUTPR)
/OUT_R_N: C67.2, L4.1, U8.21 (OUTNL)
/OUT_R_P: C66.2, L3.1, U8.23 (OUTPL)
/PD_CFG1: R1.1, U1.9 (CFG1)
/PD_PG: Q4.2 (E), R4.1, U1.10 (PG), U5.26 (IO4)
/PD_SCL: R2.1, U1.2 (CFG2/SCL)
/PD_SDA: R3.1, U1.3 (CFG3/SDA)
/PSW_B: Q4.1 (B), R7.2
/PSW_G: C19.2, Q1.4 (G), R5.2, R6.1, R15.1
/PSW_MILLER: C2.1, R15.2
/PSW_PULL: Q4.3 (C), R6.2
/PVDD_EN: R7.1, R8.1, U5.30 (IO18)
/PVDD_SENSE: C18.1, R17.2, R18.1, U5.5 (SENSOR_VN)
/Q2_B: Q2.1 (B), R24.2
/Q3_B: Q3.1 (B), R25.2
/RTS: Q2.2 (E), R25.1, U6.14 (~RTS)
/SPK_L_N: C69.1, J5.1, J5.2, L2.2
/SPK_L_P: C68.1, J4.1, J4.2, L1.2, R66.1
/SPK_R_N: C71.1, J7.1, J7.2, L4.2
/SPK_R_P: C70.1, J6.1, J6.2, L3.2, R68.1
/SUB_L: D5.1, J3.1, Q13.3 (D), R36.2, R37.1
/SUB_L_AC: C47.2, R36.1
/SUB_L_RAW: C47.1, U7.15 (LOUT2)
/SUB_MUTE: Q12.3 (C), Q13.1 (G), Q14.1 (G), Q15.1 (G), R82.2
/SUB_R: D6.1, J3.3, Q15.3 (D), R38.2, R39.1
/SUB_R_AC: C48.2, R38.1
/SUB_R_RAW: C48.1, U7.14 (ROUT2)
/TAP_L: C81.1, C82.1, R66.2, R67.1
/TAP_L_C: C82.2, U7.22 (LIN2)
/TAP_R: C83.1, C84.1, R68.2, R69.1
/TAP_R_C: C84.2, U7.21 (RIN2)
/U0RXD: J8.3, U5.34 (RXD0), U6.2 (TXD)
/U0TXD: J8.1, U5.35 (TXD0), U6.3 (RXD)
/USB_DM: D8.1, J1.A7 (DN1), J1.B7 (DN2), U6.6 (UD-)
/USB_DP: D7.1, J1.A6 (DP1), J1.B6 (DP2), U6.5 (UD+)
/VBUS_SENSE: C17.1, R13.2, R14.1, U5.6 (IO34)
GND: C1.2, C3.2, C4.2, C5.2, C7.2, C8.2, C10.2, C11.2, C12.2, C13.2, C15.2, C16.2, C17.2, C18.2, C20.2, C21.2, C22.2, C23.2, C24.2, C25.2, C26.2, C30.2, C31.2, C32.2, C33.2, C34.2, C35.2, C36.2, C37.2, C38.2, C39.2, C40.2, C42.2, C45.2, C50.2, C51.2, C52.2, C53.2, C54.2, C55.2, C56.2, C57.2, C58.2, C59.2, C61.2, C63.2, C68.2, C69.2, C70.2, C71.2, C80.2, C81.2, C83.2, C90.2, D1.2 (A), D2.2 (K), D3.2, D4.2, D5.2, D6.2, D7.2, D8.2, J1.1 (EH), J1.2 (EH), J1.3 (EH), J1.4 (EH), J1.A1B12 (GND), J1.B1A12 (GND), J2.2, J3.2, J8.2, Q12.2 (E), Q14.3 (D), R1.2, R8.2, R10.2, R12.2, R14.2, R16.2, R18.2, R31.2, R34.2, R37.2, R39.2, R50.2, R52.2, R67.2, R69.2, R81.2, SW1.3 (C), SW1.4 (D), SW2.3 (C), SW2.4 (D), SW3.3 (C), SW3.4 (D), U1.11 (GND), U2.1 (GND), U3.2 (GND), U4.2 (GND), U5.1 (GND), U5.15 (GND), U5.38 (GND), U5.39 (GND), U6.1 (GND), U7.4 (DGND), U7.13 (HPGND), U7.18 (AGND), U7.26 (CE), U7.29 (EP), U8.1 (MODSEL), U8.9 (GND), U8.12 (MUTE), U8.13 (AM2), U8.14 (AM1), U8.15 (AM0), U8.22 (GND), U8.25 (GND), U8.28 (GND), U8.33 (EP), U9.2 (GND); also elsewhere on the board
IR_VCC: C80.1, R65.2, U9.3 (VCC)
PVDD: C2.2, C51.1, C52.1, C53.1, C54.1, C55.1, C56.1, C57.1, C58.1, C59.1, Q1.5 (D), Q1.6 (D), Q1.7 (D), Q1.8 (D), R16.1, R17.1, U8.17 (AVCC), U8.18 (PVCC), U8.19 (PVCC), U8.31 (PVCC), U8.32 (PVCC)
VBUS: C1.1, C3.1, C4.1, C5.1, C19.1, D1.1 (K), J1.A4B9 (VBUS), J1.B4A9 (VBUS), Q1.1 (S), Q1.2 (S), Q1.3 (S), R5.1, R13.1, U1.1 (VHV), U1.8 (VBUS), U2.3 (VIN)

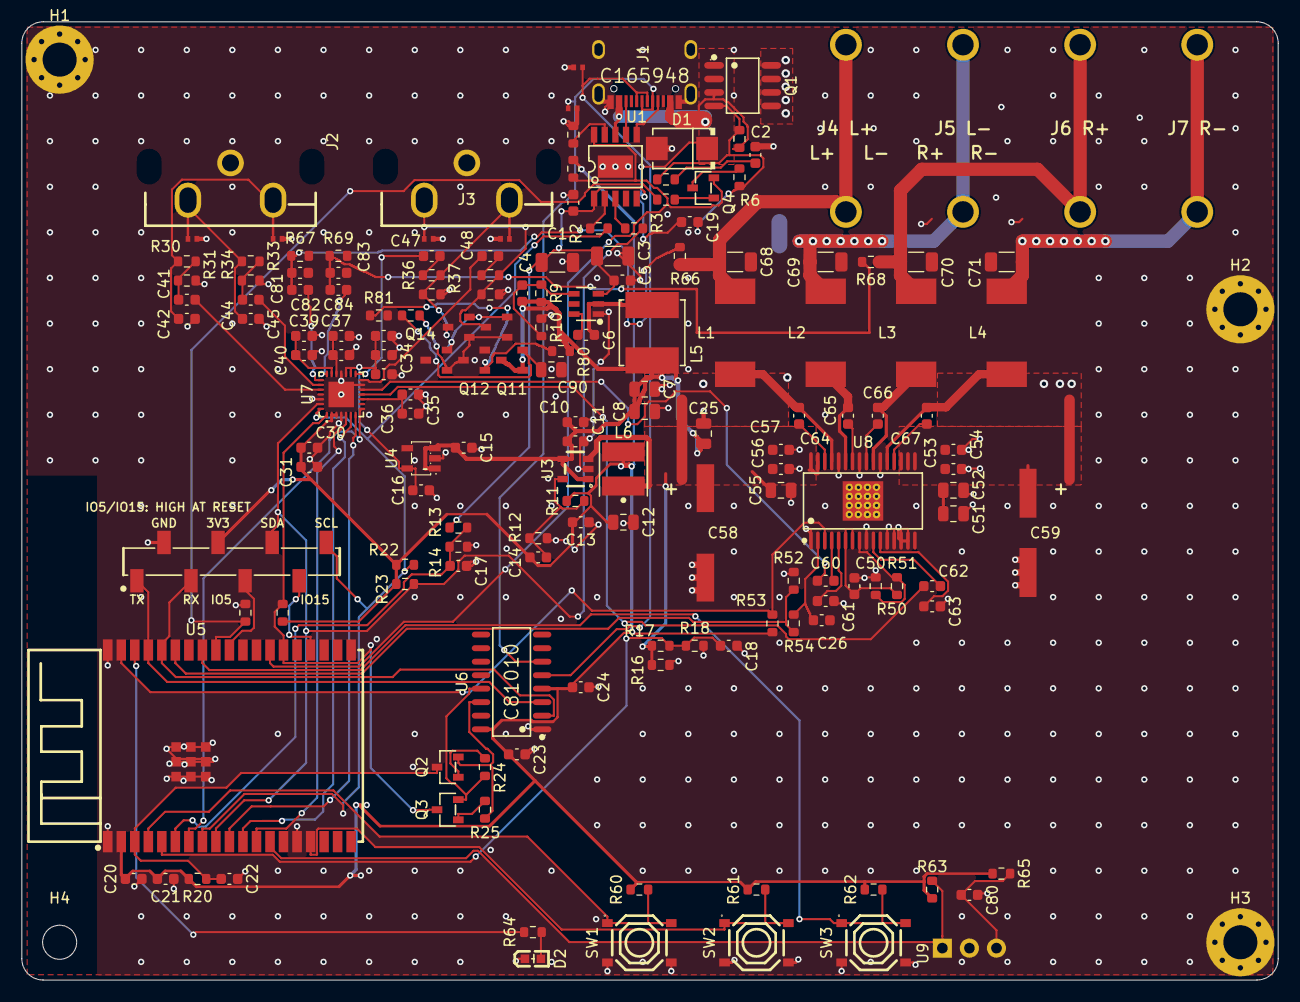
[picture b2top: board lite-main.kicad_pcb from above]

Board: 2 copper layers, 118.0 x 90.0 mm, 168 parts (0 on the bottom side), 95 nets.

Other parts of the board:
H1, H2, H3: MountingHole_3.2mm_M3_Pad_Via
H4: MountingHole_3.2mm_M3

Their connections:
GND: H1.1, H2.1, H3.1; also elsewhere on the board

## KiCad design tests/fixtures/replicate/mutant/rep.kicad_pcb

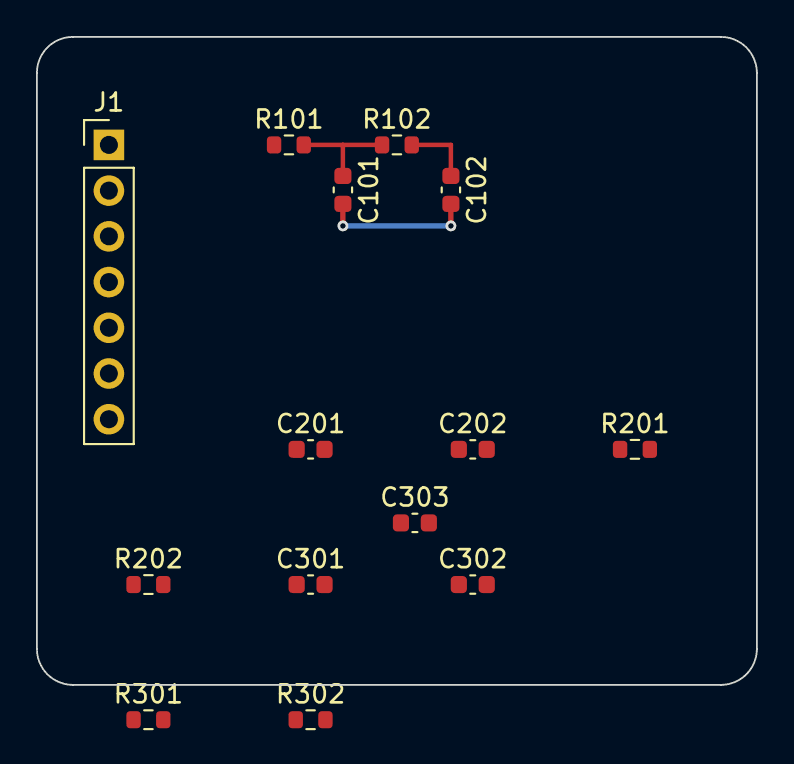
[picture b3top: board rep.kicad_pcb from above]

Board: 2 copper layers, 40.0 x 36.0 mm, 14 parts (0 on the bottom side), 10 nets.

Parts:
C101, C102, C201, C202, C301, C302: 10n; C_0603_1608Metric
C303: 100n; C_0603_1608Metric
J1: Conn_01x07; PinHeader_1x07_P2.54mm_Vertical
R101, R102, R201, R202, R301, R302: 1k; R_0603_1608Metric

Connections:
/GND: C101.2, C102.2, C201.2, C202.2, C301.2, C302.2, C303.2, J1.7
/IN1: J1.1, R101.1
/IN2: J1.2, R201.1
/IN3: J1.3, R301.1
/OUT1: C102.1, J1.4, R102.2
/OUT2: C202.1, J1.5, R202.2
/OUT3: C302.1, J1.6, R302.2
/ch1/MID: C101.1, R101.2, R102.1
/ch2/MID: C201.1, R201.2, R202.1
/ch3/MID: C301.1, C303.1, R301.2, R302.1
